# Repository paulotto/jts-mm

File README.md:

<!--
This file is part of JTS-MM (https://github.com/paulotto/jts-mm).
SPDX-FileCopyrightText: 2026 Paul-Otto Müller
SPDX-License-Identifier: CC-BY-4.0
-->

# JTS-MM: open-source multimodal jaw tracking system

JTS-MM records jaw motion, masticatory muscle activity, and inertial signals on one hardware
clock. Two low-cost global-shutter cameras track fiducial markers on the lower teeth and the
head (six degrees of freedom), a custom Raspberry Pi 5 HAT samples six channels of surface
electromyography (sEMG) and two inertial measurement units (IMUs), and one microcontroller
triggers the cameras and stamps every sample.

This repository holds the hardware, the firmware, the recording software, and the analysis
code of the studies that use the system. It extends the optical jaw tracking system of

> P.-O. Müller, S. Suppelt, M. Kupnik, O. von Stryk, "An Optical Measurement System for
> Open-Source Tracking of Jaw Motions", 2025 IEEE SENSORS,
> doi: [10.1109/SENSORS59705.2025.11330651](https://doi.org/10.1109/SENSORS59705.2025.11330651)
> ([paulotto/jaw_tracking_system](https://github.com/paulotto/jaw_tracking_system)).

## What you can do with it

| Goal | Start here |
|---|---|
| Build the system | [`docs/README.md`](docs/README.md) (reading order), `hardware/jtsmm_hat/` (KiCad), `hardware/mechanical/` (printed parts), `firmware/jtsmm/` |
| Record | [`software/jtsmm/README.md`](software/jtsmm/README.md), [`software/optical/README.md`](software/optical/README.md), `docs/operations/` |
| Analyse recordings | [`software/biomech/README.md`](software/biomech/README.md), [`docs/analysis/README.md`](docs/analysis/README.md) |
| Decode movement intent | [`software/ml/README.md`](software/ml/README.md), `docs/ml/` |
| Check a number of a paper | the paper-to-code map below |

## Papers and where their analysis lives

Three manuscripts use this repository. Each analysis has a study folder with its
configuration, its analysis plan, and the declarations of every figure, table, and number.

| Paper | Study folder | Plan and change log | Outputs |
|---|---|---|---|
| Data set: jaw exoskeleton requirements from kinematics, wearable sensing, and muscle timing | `experiments/icorr2027/` | `analysis_plan.md` (as frozen), `change_log.md` | `paper_dataset.yaml`, `numbers_dataset.yaml`, `supplementary_results/` |
| Camera-free: jaw tracking with two IMUs against the optical reference | `experiments/icorr2027/` | the same plan, analysis X5 | `paper_camerafree.yaml`, `numbers_dataset.yaml` |
| System: JTS-MM and its validation against commercial reference systems | `experiments/jtsmm_validation/` | `analysis_plan.md` (as frozen), `change_log.md` | `paper_systems.yaml`, `numbers_systems.yaml` |

Every figure, table, and in-text number of the papers is generated from a declaration in
these files by `biomech export`. The methods are documented per pipeline stage in
`docs/analysis/`.

Each analysis plan is published as it was frozen, before any outcome was computed. Its
`change_log.md` lists every later change in one row: amendments, corrected errors, deviations,
and added analyses, each with its reason and with whether results had been seen. Analyses that
were added after the freeze have a script in `scripts/audit_recompute/` and an entry in the
change log.

`experiments/icorr2027/supplementary_results/` holds the supplementary figures and tables of
the data-set paper with the data behind them, and names the frozen snapshot of the processed
data with its checksum.

**Versions.** This repository has one commit per release and no development history. The
papers and the items in `supplementary_results/` name the commit of the working repository
from which they were exported: `865fa319`. This release was built from commit
`e7d71426` of the working repository, and the build checks that the analysis code
is identical in both.

**Hash of the analysis code:** `555904d8898fc557`. Every result carries the hash of the analysis
source that computed it. The frozen snapshots of the papers (dataset `r17a`, analysis of record `r17`, validation `v15`) carry this hash,
and this repository computes the same one:

```bash
python -c "from biomech import pipeline; print(pipeline.code_hash())"
```

## Data

The recordings are not part of this repository. They are available from the authors on
request, and a data descriptor is planned.

## What this release leaves out

- **Participant files.** The files that describe individual participants (cohort files,
  session names, recording dates) belong to the data. Passages of the documentation that
  named them are shortened and marked.
- **Working material.** Internal work plans, review notes, the bench bring-up code that the
  firmware replaced, concept studies, and third-party datasheets and manufacturer 3D models
  stay in the working repository. Some documents still mention such files.
- **Paper targets of the Makefiles.** Targets that export or check the papers
  (`paper-*`, `verify`, `sync-paper*`) need the processed data and the manuscripts.

Without the recordings you can still run the complete pipeline on a synthetic study with a
known truth:

```bash
biomech synth --out /tmp/jtsmm_synth        # writes sessions, cohort, study.yaml, and runs every stage
```

## Installation and tests

Python 3.10 or newer. From the repository root:

```bash
# the Makefiles and the script tests of the recorder look for the environment at this path
python -m venv software/jtsmm/.venv && . software/jtsmm/.venv/bin/activate
pip install -e "software/jtsmm[analysis,dev]" -e software/jaw_tracking \
    -e "software/biomech[all,dev]" -e "software/ml[dev]" -e "software/optical[dev]"
pytest software/biomech                      # fast suite; add -m "slow or ml or not slow" for all
pytest software/optical/tests
pytest software/ml
pytest software/jtsmm
```

The firmware has its own build and host tests (`firmware/jtsmm/README.md`). The recorder runs
on a Raspberry Pi 5 (`scripts/install_pi.sh`).

## Contents

| Path | Contents | Papers | Licence |
|---|---|---|---|
| `firmware/jtsmm/third_party/cjson` | cJSON parser used by the firmware (third party). | systems | MIT |
| `firmware/jtsmm/pio/ws2812.pio` | WS2812 PIO program from the Raspberry Pi Pico examples (third party). | systems | BSD-3-Clause |
| `software/jtsmm/viewer_web/vendor/three.module.js` | three.js for the live viewer (third party). | systems | MIT |
| `software/jtsmm/viewer_web/vendor/uPlot*` | uPlot for the live viewer (third party). | systems | MIT |
| `software/jaw_tracking` | Jaw-kinematics pipeline of the first-generation optical system (IEEE SENSORS 2025), vendored; keeps its licence CC BY-NC-SA 4.0. | systems, data set, camera-free | CC-BY-NC-SA-4.0 |
| `pyproject.toml`<br>`requirements.txt`<br>`requirements_pi.txt`<br>`…` | Repository-wide configuration and the documentation link test. | all | MIT |
| `docs/README.md`<br>`docs/pdf/jtsmm_docs.pdf`<br>`docs/00_overview.md`<br>`…` | Documentation index, system overview, architecture, and components. | all | CC-BY-4.0 |
| `firmware/jtsmm` | RP2350 firmware of the HAT: acquisition, master clock, USB framing. | systems | MIT |
| `hardware/jtsmm_hat`<br>`hardware/jtsmm_hat_schematics.pdf` | KiCad project of the Raspberry Pi 5 HAT: schematic, PCB, libraries, production files, EEPROM. | systems | CERN-OHL-P-2.0 |
| `hardware/mechanical/viewer/vendor` | OrbitControls of three.js for the 3D viewer of the parts (third party). | systems | MIT |
| `hardware/mechanical/analyses/**/scripts`<br>`hardware/mechanical/viewer/index.html`<br>`hardware/mechanical/viewer/viewer.js`<br>`…` | Scripts of the design and concept studies of the tooth attachment, and the 3D viewer of the parts. | systems | MIT |
| `hardware/mechanical/analyses` | Design and concept studies of the tooth attachment (report, figures, CAD exports). | systems | CC-BY-4.0 |
| `hardware/mechanical/tools`<br>`hardware/mechanical/Makefile`<br>`hardware/mechanical/.gitignore` | Scripts that build the parts tables, renders and variants from the FreeCAD files. | systems, data set | MIT |
| `hardware/mechanical/*.md`<br>`hardware/mechanical/tables`<br>`hardware/mechanical/renders`<br>`…` | Parts tables, renders and figures of the 3D-printed parts. | systems, data set | CC-BY-4.0 |
| `hardware/mechanical` | 3D-printed parts: teeth attachment, markers, calibration tool (FreeCAD, STL, print files, parts.yaml). | systems, data set | CERN-OHL-P-2.0 |
| `scripts/bench` | EMG bench measurements (noise, impedance). | systems | MIT |
| `hardware/bench` | Results of the EMG bench measurements. | systems | CC-BY-4.0 |
| `software/jtsmm` | Raspberry Pi 5 host software: multimodal capture, configuration, HDF5 sessions, live viewer. | systems, data set, camera-free | MIT |
| `software/optical` | Optical tracking: multi-camera ArUco calibration and pose estimation. | systems, data set, camera-free | MIT |
| `schema` | Configuration schema shared by firmware and host. | systems | MIT |
| `aruco_markers` | ArUco marker images. | systems | CC-BY-4.0 |
| `scripts/build_install.sh`<br>`scripts/check_session_integrity.sh`<br>`scripts/flash_swd.sh`<br>`…` | Installation, flashing and network scripts of the recorder. | systems | MIT |
| `docs/calibration_validation/*.py` | Simulation scripts of the synchronisation estimate. | systems | MIT |
| `docs/hardware`<br>`docs/software`<br>`docs/optical`<br>`…` | Hardware, software, optical, calibration and operation documentation. | systems | CC-BY-4.0 |
| `experiments/5_*`<br>`experiments/data` | Evaluation scripts of the system experiments (accuracy, marker size, pivot, hand-eye, timing, EMG, IMU); smoke-tested by the biomech tests. | systems | MIT |
| `experiments/jtsmm_validation` | Validation study against Qualisys and Delsys: study configuration, analysis plan, paper numbers. | systems | MIT |
| `experiments/jtsmm_validation/*.md` | Analysis plan of the validation study. | systems | CC-BY-4.0 |
| `software/biomech` | Analysis pipeline: kinematics, EMG, IMU, statistics, figures and paper export. | data set, camera-free, systems | MIT |
| `software/ml` | Intent decoding: features, models, offline and simulated real-time evaluation. | data set, camera-free | MIT |
| `experiments/icorr2027/study.yaml`<br>`experiments/icorr2027/Makefile`<br>`experiments/icorr2027/numbers_dataset.yaml`<br>`…` | Data-set study: configuration, paper sets, numbers and captions of both papers. | data set, camera-free | MIT |
| `experiments/icorr2027/README.md`<br>`experiments/icorr2027/analysis_plan.md`<br>`experiments/icorr2027/change_log.md`<br>`…` | Analysis plan of the data-set study and the supplementary results of the JNER paper. | data set, camera-free | CC-BY-4.0 |
| `scripts/audit_recompute` | Scripts of the analyses added after the plan was frozen; they write the result files that the derived tables of the paper exports read. | data set, camera-free, systems | MIT |
| `docs/analysis`<br>`docs/ml` | Method documentation of the analysis and the decoder. | data set, camera-free, systems | CC-BY-4.0 |

Papers: *systems* = the JTS-MM system and its validation against commercial reference
systems. *data set* = the multimodal jaw-motion study. *camera-free* = jaw tracking from the
IMUs alone.

## How to cite

Please cite the article that describes what you use, and this repository for the system and
the code (see [`CITATION.cff`](CITATION.cff)). Every release is archived on Zenodo:
[10.5281/zenodo.24275718](https://doi.org/10.5281/zenodo.24275718) resolves to the latest
version, and each version has its own DOI (version 1.0.2, cited by the papers:
[10.5281/zenodo.24283858](https://doi.org/10.5281/zenodo.24283858); version 1.0.1:
[10.5281/zenodo.24281877](https://doi.org/10.5281/zenodo.24281877); version 1.0.0:
[10.5281/zenodo.24275719](https://doi.org/10.5281/zenodo.24275719)). Cite the version you used.

## Licence

Every file states its copyright and licence in an SPDX header. Files that cannot carry a
header (binary, CSV, JSON, CAD) are listed in [`REUSE.toml`](REUSE.toml). The licence texts
are in [`LICENSES/`](LICENSES/).

| Licence | Applies to |
|---|---|
| MIT | software, firmware, scripts, tests and configuration |
| CERN-OHL-P-2.0 | hardware design files (KiCad, FreeCAD, STL, print and production files) |
| CC-BY-4.0 | documentation, figures, renders and result tables |
| MIT | cJSON parser used by the firmware (third party). © 2009-2017 Dave Gamble and cJSON contributors |
| BSD-3-Clause | WS2812 PIO program from the Raspberry Pi Pico examples (third party). © 2020 Raspberry Pi (Trading) Ltd. |
| MIT | three.js for the live viewer (third party). © 2010-2023 Three.js Authors |
| MIT | uPlot for the live viewer (third party). © 2016-2024 Leon Sorokin |
| CC-BY-NC-SA-4.0 | Jaw-kinematics pipeline of the first-generation optical system (IEEE SENSORS 2025), vendored; keeps its licence CC BY-NC-SA 4.0. |
| MIT | OrbitControls of three.js for the 3D viewer of the parts (third party). © 2010-2023 Three.js Authors |

## Acknowledgement

Partially funded by the Deutsche Forschungsgemeinschaft (DFG, German Research Foundation),
project number 450821862 (Research Training Group 2761 LokoAssist).

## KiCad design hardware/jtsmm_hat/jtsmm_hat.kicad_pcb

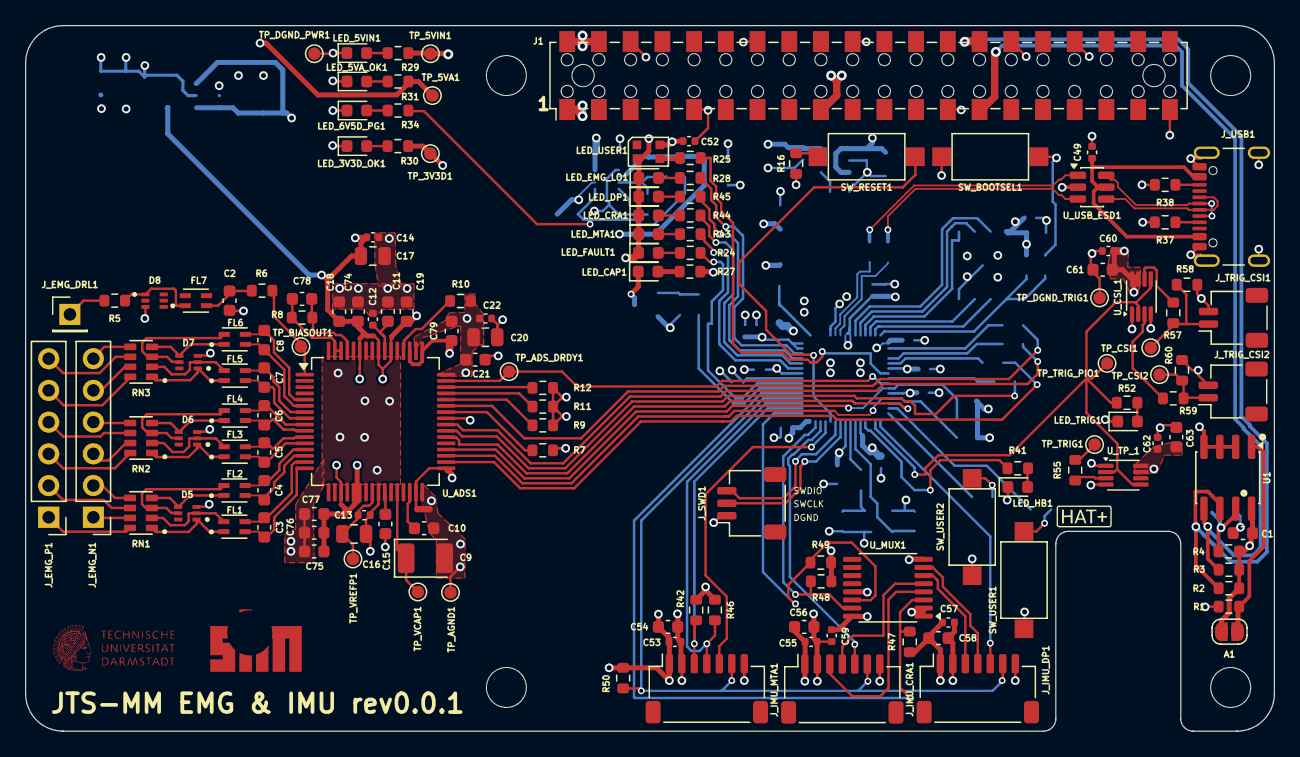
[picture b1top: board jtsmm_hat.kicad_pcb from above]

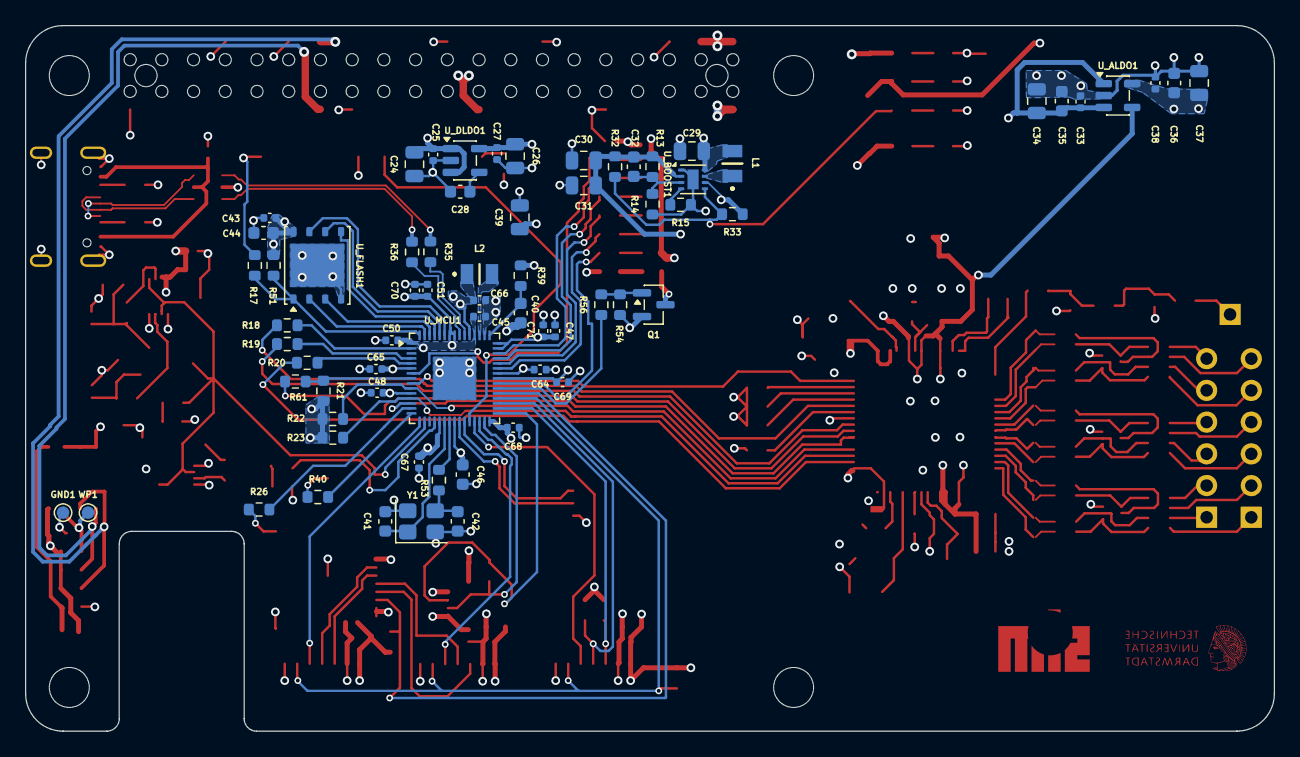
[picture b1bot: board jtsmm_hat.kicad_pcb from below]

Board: 4 copper layers, 100.0 x 56.5 mm, 216 parts (68 on the bottom side), 153 nets.

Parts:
A1: SolderJumper_2_Open; SolderJumper-2_P1.3mm_Open_RoundedPad1.0x1.5mm
C1: 100nF; C_0603_1608Metric
C2, C3, C4, C5, C6, C7, C8: 4.7nF; C_0603_1608Metric
C9: 100uF; CP_EIA-3528-21_Kemet-B
C10, C11, C15, C18, C19, C21, C44, C54, C56, C58, C61, C63, C74, C75, C76, C77, C79: 1uF; C_0603_1608Metric
C12, C13, C14, C22, C25, C27: 0.1uF; C_0402_1005Metric
C16, C17, C20, C24, C26, C29, C34, C37, C39: 10uF; C_0805_2012Metric
C28: 10nF; C_0603_1608Metric
C30, C31: 22uF; C_0805_2012Metric
C32: 100pF; C_0603_1608Metric
C33, C38, C43, C47, C48, C49, C50, C51, C52, C53, C55, C57, C59, C60, C62, C64, C65, C67, C68, C69, C70, C71: 100nF; C_0402_1005Metric
C35, C36: 2.2uF; C_0603_1608Metric
C40, C46: 4.7uF; C_0603_1608Metric
C41, C42: 15pF; C_0603_1608Metric
C45, C66: 4.7uF; C_0402_1005Metric
C78: 1.5nF; C_0603_1608Metric
D5, D6, D7, D8: TPD4E1B06; TPD4E1B06DRLR_SOT50P160X60-6N
FL1, FL2, FL3, FL4, FL5, FL6, FL7: DLW21SN900SQ2; FIL_Murata_DLW21SN900SQ2L
GND1: TestPoint_Alt; TestPoint_Pad_D1.0mm
H1, H2, H3, H4: MountingHole 3.2mm; MountingHole_3.2mm_M3_DIN965
J1: Conn_02x20_Odd_Even; Samtec_HLE-120-02-xxx-DV-BE-A_2x20_P2.54mm_Horizontal_Rever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
J_EMG_DRL1: Conn_01x01_Pin; PinHeader_1x01_P2.54mm_Vertical
J_EMG_N1: Conn_01x06_Pin; PinHeader_1x06_P2.54mm_Vertical
J_EMG_P1: Conn_01x06_Pin; PinHeader_1x06_P2.54mm_Vertical
J_IMU_CRA1: Conn_01x07_Pin; JST_SH_SM07B-SRSS-TB_1x07-1MP_P1.00mm_Horizontal
J_IMU_DP1: Conn_01x07_Pin; JST_SH_SM07B-SRSS-TB_1x07-1MP_P1.00mm_Horizontal
J_IMU_MTA1: Conn_01x07_Pin; JST_SH_SM07B-SRSS-TB_1x07-1MP_P1.00mm_Horizontal
J_SWD1: Conn_01x03_Pin; JST_SH_SM03B-SRSS-TB_1x03-1MP_P1.00mm_Horizontal
J_TRIG_CSI1, J_TRIG_CSI2: Conn_01x02_Pin; JST_SH_SM02B-SRSS-TB_1x02-1MP_P1.00mm_Horizontal
J_USB1: USB_C_Receptacle_USB2.0_16P; USB_C_Receptacle_GCT_USB4105-xx-A_16P_TopMnt_Horizontal
L1: 1uH; AOTAB201610S3R3101T
L2: 3.3uH; AOTAB201610S3R3101T
LED_3V3D_OK1: LED_3V3D_OK_Green; LED_0603_1608Metric
LED_5VA_OK1: LED_5VA_OK_Green; LED_0603_1608Metric
LED_5VIN1: LED_5VIN_Green; LED_0603_1608Metric
LED_6V5D_PG1: LED_6V5D_PG_Green; LED_0603_1608Metric
LED_CAP1: LED_CAP_Blue; LED_0603_1608Metric
LED_CRA1: LED_CRA_GREEN; LED_0603_1608Metric
LED_DP1: LED_DP_GREEN; LED_0603_1608Metric
LED_EMG_LO1: LED_EMG_LO_Yellow; LED_0603_1608Metric
LED_FAULT1: LED_FAULT_Red; LED_0603_1608Metric
LED_HB1: LED_HB_GREEN; LED_0603_1608Metric
LED_MTA1: LED_MTA_GREEN; LED_0603_1608Metric
LED_TRIG1: LED_TRIG_Amber; LED_0603_1608Metric
LED_USER1: LED_USER_RGB; LED_WS2812B-2020_PLCC4_2.0x2.0mm
NT_GND_TIE1: NetTie_2; NetTie-2_SMD_Pad0.5mm
Q1: AO3400A; SOT-23
R1, R2, R3, R4: 3.9k; R_0603_1608Metric
R5, R56: 100; R_0603_1608Metric
R6: 220k; R_0603_1608Metric
R7, R9, R10, R11, R12, R21, R22, R23, R47, R50, R51: 10k; R_0603_1608Metric
R8, R32: 1M; R_0603_1608Metric
R13: 787k; R_0603_1608Metric
R14: 180k; R_0603_1608Metric
R15: 20k; R_0603_1608Metric
R16, R17, R26, R40, R53: 1k; R_0603_1608Metric
R18, R19, R20, R61: 22; R_0603_1608Metric
R24, R27, R28, R30, R34, R41, R43, R44, R45, R52: 470; R_0603_1608Metric
R25: 220; R_0603_1608Metric
R29, R31, R42, R46, R48, R49: 2.2k; R_0603_1608Metric
R33: 15k; R_0603_1608Metric
R35, R36: 27; R_0603_1608Metric
R37, R38: 5.1k; R_0603_1608Metric
R39: 33; R_0603_1608Metric
R54: 100k; R_0603_1608Metric
R55: 50; R_0603_1608Metric
R57, R59: 1.5k; R_0603_1608Metric
R58, R60: 1.8k; R_0603_1608Metric
RN1, RN2, RN3: CAY16-1000F4LF; Bourns_RESCAF80P320X160X60-8N
SW_BOOTSEL1: SW_Push_BOOTSEL; SW_SPST_CK_RS282G05A3
SW_RESET1: SW_Push_RESET; SW_SPST_CK_RS282G05A3
SW_USER1: SW_Push_USER1; SW_SPST_CK_RS282G05A3
SW_USER2: SW_Push_USER2; SW_SPST_CK_RS282G05A3
TP_3V3D1, TP_5VA1, TP_5VIN1: TestPoint; TestPoint_Pad_D1.0mm
TP_ADS_DRDY1: TestPoint; TestPoint_Pad_D1.0mm
TP_AGND1: TestPoint; TestPoint_Pad_D1.0mm
TP_BIASOUT1: TestPoint; TestPoint_Pad_D1.0mm
TP_CSI1, TP_CSI2: TestPoint; TestPoint_Pad_D1.0mm
TP_DGND_PWR1: TestPoint; TestPoint_Pad_D1.0mm
TP_DGND_TRIG1: TestPoint; TestPoint_Pad_D1.0mm
TP_TRIG1: TestPoint; TestPoint_Pad_D1.0mm
TP_TRIG_PIO1: TestPoint; TestPoint_Pad_D1.0mm
TP_VCAP1: TestPoint; TestPoint_Pad_D1.0mm
TP_VREFP1: TestPoint; TestPoint_Pad_D1.0mm
U1: AT24CS64-SSHM; SOIC-8_3.9x4.9mm_P1.27mm
U_ADS1: ADS1299IPAG; TQFP-64_10x10mm_P0.5mm
U_ALDO1: ADP7142AUJZ-5.0; TSOT-23-5
U_BOOST1: TPS61252DSG; WSON-8-1EP_2x2mm_P0.5mm_EP0.9x1.6mm
U_CSI_1: 74LVC2G241; VSSOP-8_2.3x2mm_P0.5mm
U_DLDO1: TPS73633DBV; SOT-23-5
U_FLASH1: W25Q128JVP; WSON-8-1EP_6x5mm_P1.27mm_EP3.4x4.3mm
U_MCU1: RP2350A; QFN-60-1EP_7x7mm_P0.4mm_EP3.4x3.4mm
U_MUX1: TCA9546APW; TSSOP-16_4.4x5mm_P0.65mm
U_TP_1: 74LVC2G241; VSSOP-8_2.3x2mm_P0.5mm
U_USB_ESD1: USBLC6-2SC6; SOT-23-6
WP1: TestPoint_Alt; TestPoint_Pad_D1.0mm
Y1: 12MHz; Crystal_SMD_3225-4Pin_3.2x2.5mm

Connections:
+3V3D: C20.1, C21.1, C22.1, C26.1, C27.1, C39.1, C43.2, C44.2, C45.1, C47.2, C48.2, C50.2, C51.2, C53.2, C54.2, C55.2, C56.2, C57.2, C58.2, C59.2, C60.1, C61.1, C62.1, C63.1, C67.2, C68.2, C69.2, C70.2, C71.1, C79.2, J_IMU_CRA1.1, J_IMU_DP1.1, J_IMU_MTA1.1, R10.1, R21.2, R22.2, R23.2, R30.1, R39.2, R42.2, R46.2, R47.1, R48.2, R49.2, R50.2, R51.2, TP_3V3D1.1 (1_1), U_ADS1.48 (DVDD), U_ADS1.50 (DVDD), U_CSI_1.7, U_CSI_1.8 (VCC), U_DLDO1.5 (OUT), U_FLASH1.8 (VCC), U_MCU1.1 (IOVDD), U_MCU1.11 (IOVDD), U_MCU1.20 (IOVDD), U_MCU1.30 (IOVDD), U_MCU1.38 (IOVDD), U_MCU1.44 (ADC_AVDD), U_MCU1.45 (IOVDD), U_MCU1.49 (VREG_VIN), U_MCU1.53 (USB_OTP_VDD), U_MCU1.54 (QSPI_IOVDD), U_MUX1.16 (VCC), U_TP_1.7, U_TP_1.8 (VCC)
+5VA: C14.1, C17.1, C18.1, C19.1, C36.2, C37.2, C38.2, C74.1, C75.1, C76.1, C77.1, R31.1, TP_5VA1.1 (1_1), U_ADS1.19 (AVDD), U_ADS1.21 (AVDD), U_ADS1.22 (AVDD), U_ADS1.54 (AVDD1), U_ADS1.56 (AVDD), U_ADS1.59 (AVDD), U_ALDO1.4 (SENSE/ADJ), U_ALDO1.5 (VOUT)
+5V_IN: C24.1, C25.1, C29.1, C52.2, J1.2, J1.4, L1.2, LED_USER1.4 (VDD), R27.2, R29.1, R33.1, TP_5VIN1.1 (1_1), U_BOOST1.6 (EN), U_BOOST1.8 (VIN), U_DLDO1.1 (IN), U_DLDO1.3 (EN)
+6.5V: C30.2, C31.2, C32.2, C33.2, C34.2, C35.2, R13.2, R32.2, U_ALDO1.1 (VIN), U_ALDO1.3 (EN), U_BOOST1.2 (VOUT)
/emg/ADS_DRDY: TP_ADS_DRDY1.1 (1_1), U_ADS1.47 (~DRDY), U_MCU1.9 (GPIO6)
/emg/ADS_PWDN: R23.1, U_ADS1.35 (~PWDN), U_MCU1.12 (GPIO8)
/emg/ADS_RESET: R22.1, U_ADS1.36 (~RESET), U_MCU1.10 (GPIO7)
/emg/ADS_SPI_CLK: R19.2, U_ADS1.40 (SCLK)
/emg/ADS_SPI_CS: R61.2, U_ADS1.39 (~CS)
/emg/ADS_SPI_MISO: R18.2, U_ADS1.43 (DOUT)
/emg/ADS_SPI_MOSI: R20.2, U_ADS1.34 (DIN)
/emg/ADS_START: U_ADS1.38 (START), U_MCU1.13 (GPIO9)
/emg/BIASOUT: C78.1, R8.2, U_ADS1.62 (BIASIN), U_ADS1.63 (BIASOUT)
/emg/IN1N: C3.2, FL1.3, U_ADS1.15 (IN1N)
/emg/IN1P: C3.1, FL1.2, U_ADS1.16 (IN1P)
/emg/IN2N: C4.2, FL2.3, U_ADS1.13 (IN2N)
/emg/IN2P: C4.1, FL2.2, U_ADS1.14 (IN2P)
/emg/IN3N: C5.2, FL3.3, U_ADS1.11 (IN3N)
/emg/IN3P: C5.1, FL3.2, U_ADS1.12 (IN3P)
/emg/IN4N: C6.2, FL4.3, U_ADS1.9 (IN4N)
/emg/IN4P: C6.1, FL4.2, U_ADS1.10 (IN4P)
/emg/IN5N: C7.2, FL5.3, U_ADS1.7 (IN5N)
/emg/IN5P: C7.1, FL5.2, U_ADS1.8 (IN5P)
/emg/IN6N: C8.2, FL6.3, U_ADS1.5 (IN6N)
/emg/IN6P: C8.1, FL6.2, U_ADS1.6 (IN6P)
/emg/IN8N_BIASOUT: R6.1, TP_BIASOUT1.1 (1_1), U_ADS1.1 (IN8N)
/hat_plus/GPIO0_ID_SDA0: J1.27, R3.1, U1.5 (SDA)
/hat_plus/GPIO1_ID_SCL0: J1.28, R2.1, U1.6 (SCL)
/hat_plus/HAT_3V3: A1.2 (B), C1.1, J1.1, J1.17, R2.2, R3.2, R4.2, U1.8 (VCC)
/imu_connectors/I2C_MUX_RST: R47.2, U_MCU1.35 (GPIO23), U_MUX1.3 (~RESET)
/imu_connectors/IMU_CRA_INT: J_IMU_CRA1.5, U_MCU1.28 (GPIO17)
/imu_connectors/IMU_CRA_SCL: R49.1, U_MCU1.31 (GPIO19), U_MUX1.14 (SCL)
/imu_connectors/IMU_CRA_SDA: R48.1, U_MCU1.29 (GPIO18), U_MUX1.15 (SDA)
/imu_connectors/IMU_DP_INT: J_IMU_DP1.5, U_MCU1.16 (GPIO12)
/imu_connectors/IMU_MTA_INT: J_IMU_MTA1.5, U_MCU1.27 (GPIO16)
/imu_connectors/IMU_MTA_SCL: J_IMU_MTA1.4, R46.1, U_MCU1.33 (GPIO21)
/imu_connectors/IMU_MTA_SDA: J_IMU_MTA1.3, R42.1, U_MCU1.32 (GPIO20)
/imu_connectors/IMU_NRST: J_IMU_CRA1.6, J_IMU_DP1.6, J_IMU_MTA1.6, R50.1, U_MCU1.34 (GPIO22)
/imu_connectors/LED_IMU_CRA_ACT: R44.1, U_MCU1.41 (GPIO27/ADC1)
/imu_connectors/LED_IMU_DP_ACT: R45.1, U_MCU1.42 (GPIO28/ADC2)
/imu_connectors/LED_IMU_MTA_ACT: R43.1, U_MCU1.40 (GPIO26/ADC0)
/mcu/TRIG_PIO: R52.1, TP_TRIG_PIO1.1 (1_1), U_CSI_1.2, U_CSI_1.5, U_MCU1.17 (GPIO13), U_TP_1.2, U_TP_1.5
/mcu/USB1-D+: J_USB1.A6 (D+), J_USB1.B6 (D+), U_USB_ESD1.4 (I/O2)
/mcu/USB1-D-: J_USB1.A7 (D-), J_USB1.B7 (D-), U_USB_ESD1.6 (I/O1)
/mcu/USB1-DN: R35.1, U_USB_ESD1.1 (I/O1)
/mcu/USB1-DP: R36.1, U_USB_ESD1.3 (I/O2)
/power/U4_Boost1_PG: R32.1, R33.2, R34.1, U_BOOST1.5 (PG)
AGND: C2.2, C9.2, C10.2, C11.2, C12.2, C13.2, C14.2, C15.2, C16.2, C17.2, C18.2, C19.2, C33.1, C34.1, C35.1, C36.1, C37.1, C38.1, C74.2, C75.2, C76.2, C77.2, D5.3 (GND), D6.3 (GND), D7.3 (GND), D8.3 (GND), J_IMU_CRA1.7, J_IMU_DP1.7, J_IMU_MTA1.7, NT_GND_TIE1.1, TP_AGND1.1 (1_1), U_ADS1.20 (AVSS), U_ADS1.23 (AVSS), U_ADS1.25 (VREFN), U_ADS1.32 (AVSS), U_ADS1.53 (AVSS1), U_ADS1.57 (AVSS), U_ADS1.58 (AVSS), U_ADS1.60 (BIASREF), U_ALDO1.2 (GND)
DGND: C1.2, C20.2, C21.2, C22.2, C24.2, C25.2, C26.2, C27.2, C28.2, C29.2, C30.1, C31.1, C39.2, C40.2, C41.2, C42.2, C43.1, C44.1, C45.2, C46.2, C47.1, C48.1, C49.2, C50.1, C51.1, C52.1, C53.1, C54.1, C55.1, C56.1, C57.1, C58.1, C59.1, C60.2, C61.2, C62.2, C63.2, C64.1, C65.1, C66.2, C67.1, C68.1, C69.1, C70.1, C71.2, C79.1, GND1.1 (1_1), J1.6, J1.9, J1.14, J1.20, J1.25, J1.30, J1.34, J1.39, J_IMU_CRA1.2, J_IMU_DP1.2, J_IMU_MTA1.2, J_SWD1.1, J_TRIG_CSI1.2 (XTR-), J_TRIG_CSI2.2 (XTR-), J_USB1.A1 (GND), J_USB1.A12 (GND), J_USB1.B1 (GND), J_USB1.B12 (GND), J_USB1.SH (SHIELD), LED_3V3D_OK1.1 (K), LED_5VA_OK1.1 (K), LED_5VIN1.1 (K), LED_6V5D_PG1.1 (K), LED_CRA1.1 (K), LED_DP1.1 (K), LED_EMG_LO1.1 (K), LED_FAULT1.1 (K), LED_HB1.1 (K), LED_MTA1.1 (K), LED_TRIG1.1 (K), LED_USER1.2 (VSS), NT_GND_TIE1.2, Q1.2 (S), R1.1, R7.1, R9.1, R11.1, R12.1, R14.1, R15.1, R16.2, R37.2, R38.2, R54.2, R58.2, R60.2, SW_BOOTSEL1.1, SW_USER1.2, SW_USER2.2, TP_DGND_PWR1.1 (1_1), TP_DGND_TRIG1.1 (1_1), U1.2 (A1), U1.3 (A2), U1.4 (GND), U_ADS1.31 (RESV1), U_ADS1.33 (DGND), U_ADS1.41 (DAISY_IN), U_ADS1.49 (DGND), U_ADS1.51 (DGND), U_BOOST1.1 (GND), U_BOOST1.9 (GND), U_CSI_1.1, U_CSI_1.4 (GND), U_DLDO1.2 (GND), U_FLASH1.4 (GND), U_FLASH1.9 (EP), U_MCU1.47 (VREG_PGND), U_MCU1.61 (GND), U_MUX1.1 (A0), U_MUX1.2 (A1), U_MUX1.8 (GND), U_MUX1.13 (A2), U_TP_1.1, U_TP_1.4 (GND), U_USB_ESD1.2 (GND), Y1.2 (G), Y1.4 (G)
unnamed: A1.1 (A), R1.2, U1.1 (A0)
unnamed: C2.1, FL7.2, R6.2
unnamed: C42.1, R53.1, Y1.3
unnamed: D5.1 (IO1), FL1.1, RN1.1 (R1.1)
unnamed: D5.2 (IO2), FL1.4, RN1.2 (R2.1)
unnamed: D5.4 (IO3), FL2.1, RN1.4 (R4.1)
unnamed: D5.5 (IO4), FL2.4, RN1.3 (R3.1)
unnamed: D6.1 (IO1), FL3.1, RN2.1 (R1.1)
unnamed: D6.2 (IO2), FL3.4, RN2.2 (R2.1)
unnamed: D6.4 (IO3), FL4.1, RN2.4 (R4.1)
unnamed: D6.5 (IO4), FL4.4, RN2.3 (R3.1)
unnamed: D7.1 (IO1), FL5.1, RN3.1 (R1.1)
unnamed: D7.2 (IO2), FL5.4, RN3.2 (R2.1)
unnamed: D7.4 (IO3), FL6.1, RN3.4 (R4.1)
unnamed: D7.5 (IO4), FL6.4, RN3.3 (R3.1)
unnamed: D8.1 (IO1), FL7.1, R5.1
unnamed: J_EMG_DRL1.1 (DRL_1), R5.2
unnamed: J_EMG_N1.1 (IN1N), RN1.7 (R2.2)
unnamed: J_EMG_N1.2 (IN2N), RN1.5 (R4.2)
unnamed: J_EMG_N1.3 (IN3N), RN2.7 (R2.2)
unnamed: J_EMG_N1.4 (IN4N), RN2.5 (R4.2)
unnamed: J_EMG_N1.5 (IN5N), RN3.7 (R2.2)
unnamed: J_EMG_N1.6 (IN6N), RN3.5 (R4.2)
unnamed: J_EMG_P1.1 (IN1P), RN1.8 (R1.2)
unnamed: J_EMG_P1.2 (IN2P), RN1.6 (R3.2)
unnamed: J_EMG_P1.3 (IN3P), RN2.8 (R1.2)
unnamed: J_EMG_P1.4 (IN4P), RN2.6 (R3.2)
unnamed: J_EMG_P1.5 (IN5P), RN3.8 (R1.2)
unnamed: J_EMG_P1.6 (IN6P), RN3.6 (R3.2)
unnamed: J_IMU_CRA1.3, U_MUX1.4 (SD0)
unnamed: J_IMU_CRA1.4, U_MUX1.5 (SC0)
unnamed: J_IMU_DP1.3, U_MUX1.6 (SD1)
unnamed: J_IMU_DP1.4, U_MUX1.7 (SC1)
unnamed: J_SWD1.2, U_MCU1.24 (SWCLK)
unnamed: J_SWD1.3, U_MCU1.25 (SWDIO)
unnamed: J_TRIG_CSI1.1 (XTR+), R57.2, R58.1, TP_CSI1.1 (1_1)
unnamed: J_TRIG_CSI2.1 (XTR+), R59.2, R60.1, TP_CSI2.1 (1_1)
unnamed: J_USB1.A5 (CC1), R37.1
unnamed: J_USB1.B5 (CC2), R38.1
unnamed: LED_3V3D_OK1.2 (A), R30.2
unnamed: LED_5VA_OK1.2 (A), R31.2
unnamed: LED_5VIN1.2 (A), R29.2
unnamed: LED_6V5D_PG1.2 (A), R34.2
unnamed: LED_CAP1.2 (A), R27.1
unnamed: LED_CAP1.1 (K), Q1.3 (D)
unnamed: LED_CRA1.2 (A), R44.2
unnamed: LED_DP1.2 (A), R45.2
unnamed: LED_EMG_LO1.2 (A), R28.2
unnamed: LED_FAULT1.2 (A), R24.2
unnamed: LED_HB1.2 (A), R41.2
unnamed: LED_MTA1.2 (A), R43.2
unnamed: LED_TRIG1.2 (A), R52.2
unnamed: LED_USER1.3 (DIN), R25.2
unnamed: Q1.1 (G), R54.1, R56.2
unnamed: R16.1, SW_RESET1.1
unnamed: R17.2, SW_BOOTSEL1.2
unnamed: R26.1, SW_USER1.1
unnamed: R40.1, SW_USER2.1
unnamed: R55.1, U_TP_1.3
unnamed: R55.2, TP_TRIG1.1 (1_1)
unnamed: R57.1, U_CSI_1.6
unnamed: R59.1, U_CSI_1.3
unnamed: R4.1, U1.7 (WP), WP1.1 (1_1)
unnamed: C78.2, R8.1, U_ADS1.61 (BIASINV)
unnamed: R10.2, U_ADS1.52 (CLKSEL)
unnamed: R7.2, U_ADS1.42 (GPIO1)
unnamed: R9.2, U_ADS1.44 (GPIO2)
unnamed: R11.2, U_ADS1.45 (GPIO3)
unnamed: R12.2, U_ADS1.46 (GPIO4)
unnamed: C9.1, TP_VCAP1.1 (1_1), U_ADS1.28 (VCAP1)
unnamed: C10.1, U_ADS1.30 (VCAP2)
unnamed: C11.1, C12.1, U_ADS1.55 (VCAP3)
unnamed: C15.1, U_ADS1.26 (VCAP4)
unnamed: C13.1, C16.1, TP_VREFP1.1 (1_1), U_ADS1.24 (VREFP)
unnamed: C32.1, R13.1, R14.2, U_BOOST1.3 (FB)
unnamed: R15.2, U_BOOST1.4 (ILIM)
unnamed: L1.1, U_BOOST1.7 (SW)
unnamed: C28.1, U_DLDO1.4 (NR)
unnamed: U_FLASH1.6 (CLK), U_MCU1.56 (QSPI_SCLK)
unnamed: U_FLASH1.5 (DI/IO_{0}), U_MCU1.57 (QSPI_SD0)
unnamed: U_FLASH1.2 (DO/IO_{1}), U_MCU1.59 (QSPI_SD1)
unnamed: R17.1, R51.1, U_FLASH1.1 (~CS), U_MCU1.60 (~QSPI_SS)
unnamed: U_FLASH1.7 (~HOLD/~RESET/IO_{3}), U_MCU1.55 (QSPI_SD3)
unnamed: U_FLASH1.3 (~WP/IO_{2}), U_MCU1.58 (QSPI_SD2)
unnamed: R18.1, U_MCU1.2 (GPIO0)
unnamed: R19.1, U_MCU1.4 (GPIO2)
unnamed: R20.1, U_MCU1.5 (GPIO3)
unnamed: R25.1, U_MCU1.7 (GPIO4)
unnamed: R21.1, R61.1, U_MCU1.8 (GPIO5)
unnamed: R26.2, U_MCU1.14 (GPIO10)
unnamed: R40.2, U_MCU1.15 (GPIO11)
unnamed: R41.1, U_MCU1.19 (GPIO15)
unnamed: R56.1, U_MCU1.36 (GPIO24)
unnamed: R24.1, U_MCU1.37 (GPIO25)
unnamed: R28.1, U_MCU1.43 (GPIO29/ADC3)
unnamed: SW_RESET1.2, U_MCU1.26 (RUN)
unnamed: R35.2, U_MCU1.51 (USB_DM)
unnamed: R36.2, U_MCU1.52 (USB_DP)
unnamed: C40.1, R39.1, U_MCU1.46 (VREG_AVDD)
unnamed: C46.1, C64.2, C65.2, C66.1, L2.1, U_MCU1.6 (DVDD), U_MCU1.23 (DVDD), U_MCU1.39 (DVDD), U_MCU1.50 (VREG_FB)
unnamed: L2.2, U_MCU1.48 (VREG_LX)
unnamed: C41.1, U_MCU1.21 (XIN), Y1.1
unnamed: R53.2, U_MCU1.22 (XOUT)
unnamed: C49.1, J_USB1.A4 (VBUS), J_USB1.A9 (VBUS), J_USB1.B4 (VBUS), J_USB1.B9 (VBUS), U_USB_ESD1.5 (VBUS)

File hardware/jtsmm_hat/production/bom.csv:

Designator,Footprint,Quantity,Value,LCSC Part #
C1,603,1,100nF,C77055
"C10, C11, C15, C18, C19, C21, C44, C54, C56, C58, C61, C63, C74, C75, C76, C77, C79",603,17,1uF,C15849
"C12, C13, C14, C22, C25, C27",402,6,0.1uF,C71629
"C16, C17, C20, C24, C26, C29, C34, C37, C39",805,9,10uF,C77075
"C2, C3, C4, C5, C6, C7, C8",603,7,4.7nF,C85980
C28,603,1,10nF,C77053
"C30, C31",805,2,22uF,C86817
C32,603,1,100pF,C71664
"C33, C38, C43, C47, C48, C49, C50, C51, C52, C53, C55, C57, C59, C60, C62, C64, C65, C67, C68, C69, C70, C71",402,22,100nF,C71629
"C35, C36",603,2,2.2uF,C86013
"C40, C46",603,2,4.7uF,C71633
"C41, C42",603,2,15pF,C71651
"C45, C66",402,2,4.7uF,C2858031
C78,603,1,1.5nF,C162204
C9,CP_EIA-3528-21_Kemet-B,1,100uF,C122271
"D5, D6, D7, D8",TPD4E1B06DRLR_SOT50P160X60-6N,4,TPD4E1B06,C1972953
"FL1, FL2, FL3, FL4, FL5, FL6, FL7",FIL_Murata_DLW21SN900SQ2L,7,DLW21SN900SQ2,C97856
J1,Samtec_HLE-120-02-xxx-DV-BE-A_2x20_P2.54mm_Horizontal_Reverse,1,Conn_02x20_Odd_Even,
J_EMG_DRL1,PinHeader_1x01_P2.54mm_Vertical,1,Conn_01x01_Pin,PPH1-06-UA
"J_EMG_N1, J_EMG_P1",PinHeader_1x06_P2.54mm_Vertical,2,Conn_01x06_Pin,PPH1-06-UA
"J_IMU_CRA1, J_IMU_DP1, J_IMU_MTA1",JST_SH_SM07B-SRSS-TB_1x07-1MP_P1.00mm_Horizontal,3,Conn_01x07_Pin,C160406
J_SWD1,JST_SH_SM03B-SRSS-TB_1x03-1MP_P1.00mm_Horizontal,1,Conn_01x03_Pin,C160403
"J_TRIG_CSI1, J_TRIG_CSI2",JST_SH_SM02B-SRSS-TB_1x02-1MP_P1.00mm_Horizontal,2,Conn_01x02_Pin,C160402
J_USB1,USB_C_Receptacle_GCT_USB4105-xx-A_16P_TopMnt_Horizontal,1,USB_C_Receptacle_USB2.0_16P,C3020560
L1,AOTAB201610S3R3101T,1,1uH,C25914177
L2,AOTAB201610S3R3101T,1,3.3uH,C42411119
LED_3V3D_OK1,603,1,LED_3V3D_OK_Green,C125094
LED_5VA_OK1,603,1,LED_5VA_OK_Green,C125094
LED_5VIN1,603,1,LED_5VIN_Green,C125094
LED_6V5D_PG1,603,1,LED_6V5D_PG_Green,C125094
LED_CAP1,603,1,LED_CAP_Blue,C125096
LED_CRA1,603,1,LED_CRA_GREEN,C125094
LED_DP1,603,1,LED_DP_GREEN,C125094
LED_EMG_LO1,603,1,LED_EMG_LO_Yellow,C84268
LED_FAULT1,603,1,LED_FAULT_Red,C157741
LED_HB1,603,1,LED_HB_GREEN,C125094
LED_MTA1,603,1,LED_MTA_GREEN,C125094
LED_TRIG1,603,1,LED_TRIG_Amber,C157740
LED_USER1,LED_WS2812B-2020_PLCC4_2.0x2.0mm,1,LED_USER_RGB,C965555
Q1,SOT-23,1,AO3400A,C20917
"R1, R2, R3, R4",603,4,3.9k,C114616
"R10, R11, R12, R21, R22, R23, R47, R50, R51, R7, R9",603,11,10k,C95204
R13,603,1,787k,C246008
R14,603,1,180k,C123419
R15,603,1,20k,C2907011
"R16, R17, R26, R40, R53",603,5,1k,C21190
"R18, R19, R20, R61",603,4,22,C2930077
"R24, R27, R28, R30, R34, R41, R43, R44, R45, R52",603,10,470,C269714
R25,603,1,220,C22962
"R29, R31, R42, R46, R48, R49",603,6,2.2k,C2907117
"R32, R8",603,2,1M,C22935
R33,603,1,15k,C22809
"R35, R36",603,2,27,C137753
"R37, R38",603,2,5.1k,C105580
R39,603,1,33,C108407
"R5, R56",603,2,100,C22775
R54,603,1,100k,C25803
R55,603,1,50,C114625
"R57, R59",603,2,1.5k,C114668
"R58, R60",603,2,1.8k,C185354
R6,603,1,220k,C22961
"RN1, RN2, RN3",Bourns_RESCAF80P320X160X60-8N,3,CAY16-1000F4LF,C1852225
SW_BOOTSEL1,SW_SPST_CK_RS282G05A3,1,SW_Push_BOOTSEL,C221930
SW_RESET1,SW_SPST_CK_RS282G05A3,1,SW_Push_RESET,C221930
SW_USER1,SW_SPST_CK_RS282G05A3,1,SW_Push_USER1,C221930
SW_USER2,SW_SPST_CK_RS282G05A3,1,SW_Push_USER2,C221930
"TP_3V3D1, TP_5VA1, TP_5VIN1, TP_ADS_DRDY1, TP_AGND1, TP_BIASOUT1, TP_CSI1, TP_CSI2, TP_DGND_PWR1, TP_DGND_TRIG1, TP_TRIG1, TP_TRIG_PIO1, TP_VCAP1, TP_VREFP1",TestPoint_Pad_D1.0mm,14,TestPoint,
U1,SOIC-8_3.9x4.9mm_P1.27mm,1,AT24CS64-SSHM,C615478
U_ADS1,TQFP-64_10x10mm_P0.5mm,1,ADS1299IPAG,C476817
U_ALDO1,TSOT-23-5,1,ADP7142AUJZ-5.0,C659367
U_BOOST1,WSON-8-1EP_2x2mm_P0.5mm_EP0.9x1.6mm,1,TPS61252DSG,C128617
"U_CSI_1, U_TP_1",VSSOP-8_2.3x2mm_P0.5mm,2,74LVC2G241,C10430
U_DLDO1,SOT-23-5,1,TPS73633DBV,C28038
U_FLASH1,WSON-8-1EP_6x5mm_P1.27mm_EP3.4x4.3mm,1,W25Q128JVP,C2441427
U_MCU1,QFN-60-1EP_7x7mm_P0.4mm_EP3.4x3.4mm,1,RP2350A,C42411118
U_MUX1,TSSOP-16_4.4x5mm_P0.65mm,1,TCA9546APW,C149507
U_USB_ESD1,SOT-23-6,1,USBLC6-2SC6,C2687116
Y1,Crystal_SMD_3225-4Pin_3.2x2.5mm,1,12MHz,C20625731

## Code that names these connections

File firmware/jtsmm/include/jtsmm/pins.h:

// This file is part of JTS-MM (https://github.com/paulotto/jts-mm).
// SPDX-FileCopyrightText: 2026 Paul-Otto Müller
// SPDX-License-Identifier: MIT

/**
 * @file pins.h
 * @brief Canonical RP2350A GPIO map for jtsmm_hat.
 *
 * @details Must match docs/hardware/h05_microcontroller_firmware.md §1.1.
 *          Values are SDK GPIO numbers (not package pin numbers).
 */
#pragma once

/** @{ @name ADS1299 — SPI0 */
#define PIN_ADS_MISO   0
#define PIN_ADS_SCLK   2
#define PIN_ADS_MOSI   3
#define PIN_ADS_CS     5
#define PIN_ADS_DRDY   6  /**< Data-ready (active low). */
#define PIN_ADS_RESET  7
#define PIN_ADS_PWDN   8
#define PIN_ADS_START  9
/** @} */

/** @{ @name Panel buttons (active low, internal pull-up) */
#define PIN_SW_USER1  10
#define PIN_SW_USER2  11
/** @} */

#define PIN_LED_USER   4  /**< User RGB WS2812B-2020 (GRB order). */
#define PIN_TRIG       13 /**< Camera XTRIG out, idles at the inactive level of pulse.polarity (HIGH for imx296_fast); the TRIG LED on the same pin (active high) is lit while idle for imx296_fast. */
#define PIN_LED_FLASH  14 /**< Track A sync LED (optional / DNP on default GS HAT). */

/** @{ @name Status LEDs (0603, active high unless noted) */
#define PIN_LED_HB     15 /**< Heartbeat. */
#define PIN_LED_FAULT  25
#define PIN_LED_CAP    24 /**< Capture / streaming active. */
#define PIN_LED_MTA    26 /**< MTA IMU activity. */
#define PIN_LED_CRA    27 /**< CRA IMU activity. */
#define PIN_LED_DP     28 /**< DP IMU (unpopulated on v1). */
#define PIN_LED_EMG_LO 29 /**< EMG lead-off / fault hint. */
/** @} */

/** @{ @name IMU I2C + interrupt / reset */
#define PIN_IMU_CRA_SDA 18
#define PIN_IMU_CRA_SCL 19
#define PIN_IMU_MTA_SDA 20
#define PIN_IMU_MTA_SCL 21
#define PIN_IMU_NRST    22 /**< Shared IMU reset (active low). */
#define PIN_IMU_MTA_INT 16 /**< MTA BNO085 INT. */
#define PIN_IMU_CRA_INT 17 /**< CRA BNO085 INT. */
/** @} */

#define ADS1299_CHIP_ID 0x3E /**< Expected ADS1299 device ID register value. */
